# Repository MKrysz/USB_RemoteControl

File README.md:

# USB Remote Control

## About

The goal of this project was to make an USB dongle allowing you to remotely control your PC with your phone with minimal setup. I achieved it by combining microcontroller with USB HID interface and Bluetooth module. Thanks to utilizing standard HID interface the receiver side is plug-and-play. Only setup is needed on smartphones side, i.e. installing the app and connecting to the dongle.

## Hardware

Schematic was made in KiCad

I used STM32F103C6 MCU as it was the cheapest MCU with USB that I had. For Bluettoth connection I used JDY-33 Bluetooth module that can be easily controlled via UART interface. I also added some LEDs and buttons for showing information like state of connection.

The boards were manufactured by JLCPCB

After soldering everything and trying to test the board I found out I could get it to connect to PC via USB. After some research I found out that my MCU is one of few from STM32 family that does not embed pullup resistor on D+ line, so I had to add it. Fully assembled device is shown below:

<!-- ## Embedded Software

Embedded software was made using [STM32CubeMX](https://www.st.com/en/development-tools/stm32cubemx.html) and VSCode using [stm32-for-vscode](https://github.com/bmd-studio/stm32-for-vscode) extension.

F
**Think about what to write here (maybe smth about USB descriptor?)** -->

## Android App

Android App was made using [MIT App Inventor](https://appinventor.mit.edu/), and in design it tries to imitate classical remote control with some additional functions like send text or change current tab in a browser. Current version heavily supports controlling YTMusic web player.

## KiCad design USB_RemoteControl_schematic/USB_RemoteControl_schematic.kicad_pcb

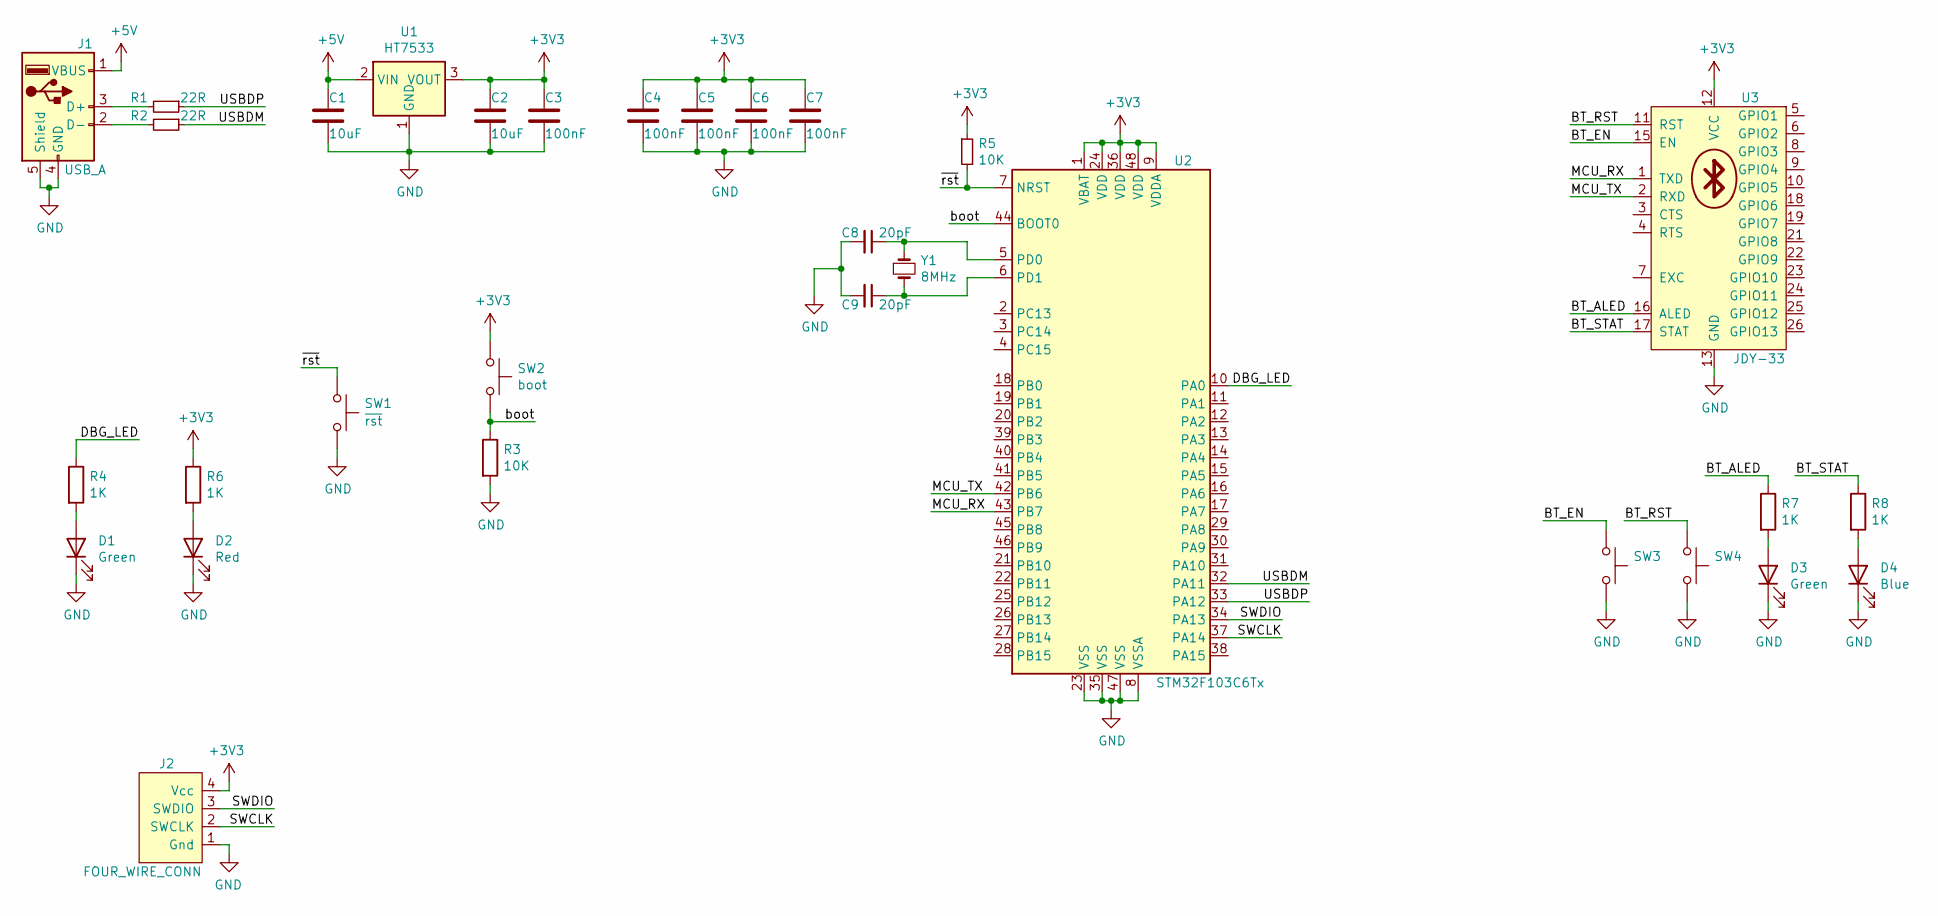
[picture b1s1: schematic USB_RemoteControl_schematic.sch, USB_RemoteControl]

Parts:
C1, C2: 10uF; C_0805_2012Metric_Pad1.18x1.45mm_HandSolder
C3, C4, C5, C6, C7: 100nF; C_0603_1608Metric_Pad1.08x0.95mm_HandSolder
C8, C9: 20pF; C_0603_1608Metric_Pad1.08x0.95mm_HandSolder
D1, D3: Green; LED_0805_2012Metric_Pad1.15x1.40mm_HandSolder
D2: Red; LED_0805_2012Metric_Pad1.15x1.40mm_HandSolder
D4: Blue; LED_0805_2012Metric_Pad1.15x1.40mm_HandSolder
J1: USB_A; USB_A_Male
J2: FOUR_WIRE_CONN; PinHeader_1x04_P2.54mm_Vertical
R1, R2: 22R; R_0805_2012Metric_Pad1.20x1.40mm_HandSolder
R3, R5: 10K; R_0805_2012Metric_Pad1.20x1.40mm_HandSolder
R4, R6, R7, R8: 1K; R_0805_2012Metric_Pad1.20x1.40mm_HandSolder
SW1: ~rst; TSB008
SW2: boot; TSB008
SW3, SW4: TSB008
U1: HT7533; SOT-89-3
U2: STM32F103C6Tx; LQFP-48_7x7mm_P0.5mm
U3: JDY-33; JDY-33, JDY-32, JDY-31, JDY-30, JDY-09
Y1: 8MHz; Crystal_SMD_HC49-SD

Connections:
+3V3: C2.1, C3.1, C4.1, C5.1, C6.1, C7.1, J2.4 (Vcc), R5.1, R6.1, SW2.1, U1.3 (VOUT), U2.1 (VBAT), U2.9 (VDDA), U2.24 (VDD), U2.36 (VDD), U2.48 (VDD), U3.12 (VCC)
+5V: C1.1, J1.1 (VBUS), U1.2 (VIN)
/BT_ALED: R7.1, U3.16 (ALED)
/BT_EN: SW3.1, U3.15 (EN)
/BT_RST: SW4.1, U3.11 (RST)
/BT_STAT: R8.1, U3.17 (STAT)
/DBG_LED: R4.1, U2.10 (PA0)
/MCU_RX: U2.43 (PB7), U3.1 (TXD)
/MCU_TX: U2.42 (PB6), U3.2 (RXD)
/SWCLK: J2.2 (SWCLK), U2.37 (PA14)
/SWDIO: J2.3 (SWDIO), U2.34 (PA13)
/USBDM: R2.1, U2.32 (PA11)
/USBDP: R1.1, U2.33 (PA12)
/boot: R3.1, SW2.2, U2.44 (BOOT0)
/~rst: R5.2, SW1.1, U2.7 (NRST)
GND: C1.2, C2.2, C3.2, C4.2, C5.2, C6.2, C7.2, C8.2, C9.2, D1.1 (K), D2.1 (K), D3.1 (K), D4.1 (K), J1.4 (GND), J1.5 (Shield), J2.1 (Gnd), R3.2, SW1.2, SW3.2, SW4.2, U1.1 (GND), U2.8 (VSSA), U2.23 (VSS), U2.35 (VSS), U2.47 (VSS), U3.13 (GND)
unnamed: C8.1, U2.5 (PD0), Y1.1
unnamed: C9.1, U2.6 (PD1), Y1.2
unnamed: D1.2 (A), R4.2
unnamed: D2.2 (A), R6.2
unnamed: D3.2 (A), R7.2
unnamed: D4.2 (A), R8.2
unnamed: J1.2 (D-), R2.2
unnamed: J1.3 (D+), R1.2

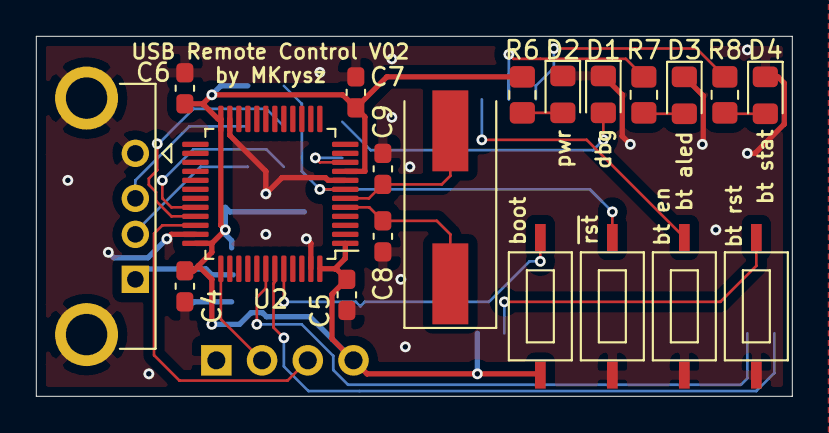
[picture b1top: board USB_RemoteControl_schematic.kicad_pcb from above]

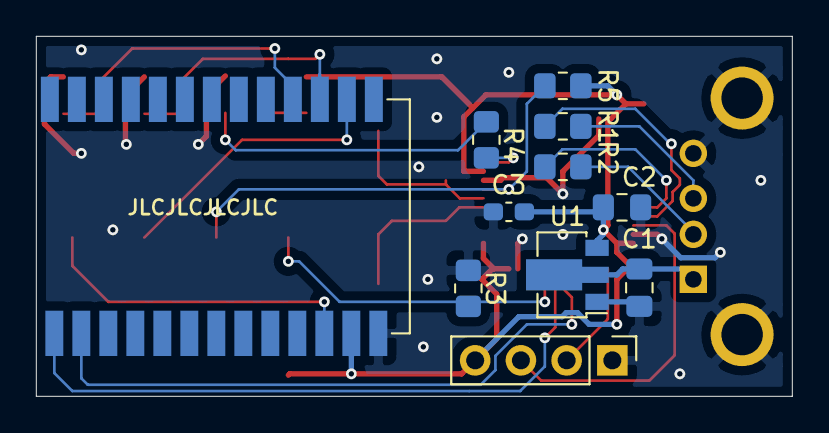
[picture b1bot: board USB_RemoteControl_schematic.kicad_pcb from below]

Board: 2 copper layers, 42.0 x 20.0 mm, 31 parts (11 on the bottom side), 24 nets.

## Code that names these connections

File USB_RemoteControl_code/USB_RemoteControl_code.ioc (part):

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Mcu.Name=STM32F103C(4-6)Tx
Mcu.Package=LQFP48
Mcu.UserName=STM32F103C6Tx
PA0-WKUP.GPIOParameters=GPIO_Label
PA0-WKUP.GPIO_Label=DBG_LED
PA0-WKUP.Signal=GPIO_Output
PA11.Mode=Device
PA11.Signal=USB_DM
PA12.Mode=Device
PA12.Signal=USB_DP
PA13.Mode=Serial_Wire
PA13.Signal=SYS_JTMS-SWDIO
PA14.Mode=Serial_Wire
PA14.Signal=SYS_JTCK-SWCLK
PB6.Mode=Asynchronous
PB6.Signal=USART1_TX
PB7.Mode=Asynchronous
PB7.Signal=USART1_RX
PD0-OSC_IN.Mode=HSE-External-Oscillator
PD0-OSC_IN.Signal=RCC_OSC_IN
PD1-OSC_OUT.Mode=HSE-External-Oscillator
PD1-OSC_OUT.Signal=RCC_OSC_OUT
RCC.SYSCLKFreq_VALUE=72000000
RCC.SYSCLKSource=RCC_SYSCLKSOURCE_PLLCLK
board=custom

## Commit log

2022-05-25 Upload Version01
2022-05-25 Completed schematic for Version02
2022-05-25 Finished PCB
2022-05-26 Added signature
2022-05-27 Generated new PCB's gerbers
2022-05-29 Improved readability of the schematic
2022-07-12 Working USB keyboard
2022-07-13 Improvements to keyboard library
2022-07-13 Working MediaControl with AHK
2022-07-14 Volume Control Works
2022-07-14 Version 2.0
2022-07-14 Added Android app
2022-07-17 Added More buttons and icon to the app
2022-07-17 Started working on README
2022-07-18 Random Movements implemented
2022-07-22 README description changed
2022-07-22 Fixed prevTab functionality not working
2022-07-22 Changed 'about' section in README
